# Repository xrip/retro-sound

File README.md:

# RP2040 Retro Sound

## What is?
RP2040 Retro Sound is a project that enables the Raspberry Pi Pico (RP2040) to serve as a COM port passthrough for various FM retro sound chips like the SAA1099, SN76489, YM3812, and YMF262. 

[Interactive BOM (bill of materials)](https://xrip.github.io/retro-sound/hardware/bom/ibom.html)

Assembled PCB:

Gerbers available via releases, or you can use whole KiCad project from ``hardware`` folder

With this setup, you can bring the authentic sound of classic gaming and computing systems to life using original sound chips. Enjoy the nostalgia of retro audio in a modern, convenient package!

## Purpose
The goal of this project is to allow enthusiasts to listen to retro sound with real sound chips without needing any other retro hardware.

## How to use
To use this project, you will need a modified version of <a href="https://github.com/xrip/retro-sound-dosbox-x/tree/master">DosBox-X</a> or a Sega Master System/Sega Genesis emulator that can passthrough sound data directly to the chips via a COM port. COM7 hardcoded right now.

The operation protocol is straightforward and consists of two-byte transfers. The first byte is the command byte:

```
/*
 * 76543210 - command byte
 * ||||||||
 * |||||||+-- chip 0 / chip 1
 * ||||||+--- address or data
 * ||||++---- reserved
 * ++++------ 0x0...0xE chip id:
 *
 *            0x0 - SN76489 (Tandy 3 voice)
 *            0x1 - YM2413 (OPLL)
 *            0x2 - YM3812 (OPL2)
 *            0x3 - SAA1099 (Creative Music System / GameBlaster)
 *            0x4 - YMF262 (OPL3)
 *            0x5 - YM2612, YM2203, YM2608, YM2610, YMF288 (OPN2 and OPN-compatible series)
 *            ...
 *            0xf - all chips reset/initialization
 */
```

The second byte is the data byte, which is routed directly to the chip.

## Requirements
1. PCB (gerbers available via releases, or you can use whole KiCad project from ``hardware`` dir)
2. RP2040 mini: The microcontroller that powers the project.
4. Retro Sound Chips: Choose from SN76489, SAA1099, YM2413, YM3812, YMF262, or any OPN2 compatible chip. The YMF262 is recommended for its versatility. 
5. Capacitors and Resistors: A few passive components for stable operation.
6. Basic Soldering Skills: Minimal soldering is required to assemble the hardware.

## Credits
PCB designs and all hardware stuff are by Sa Gin

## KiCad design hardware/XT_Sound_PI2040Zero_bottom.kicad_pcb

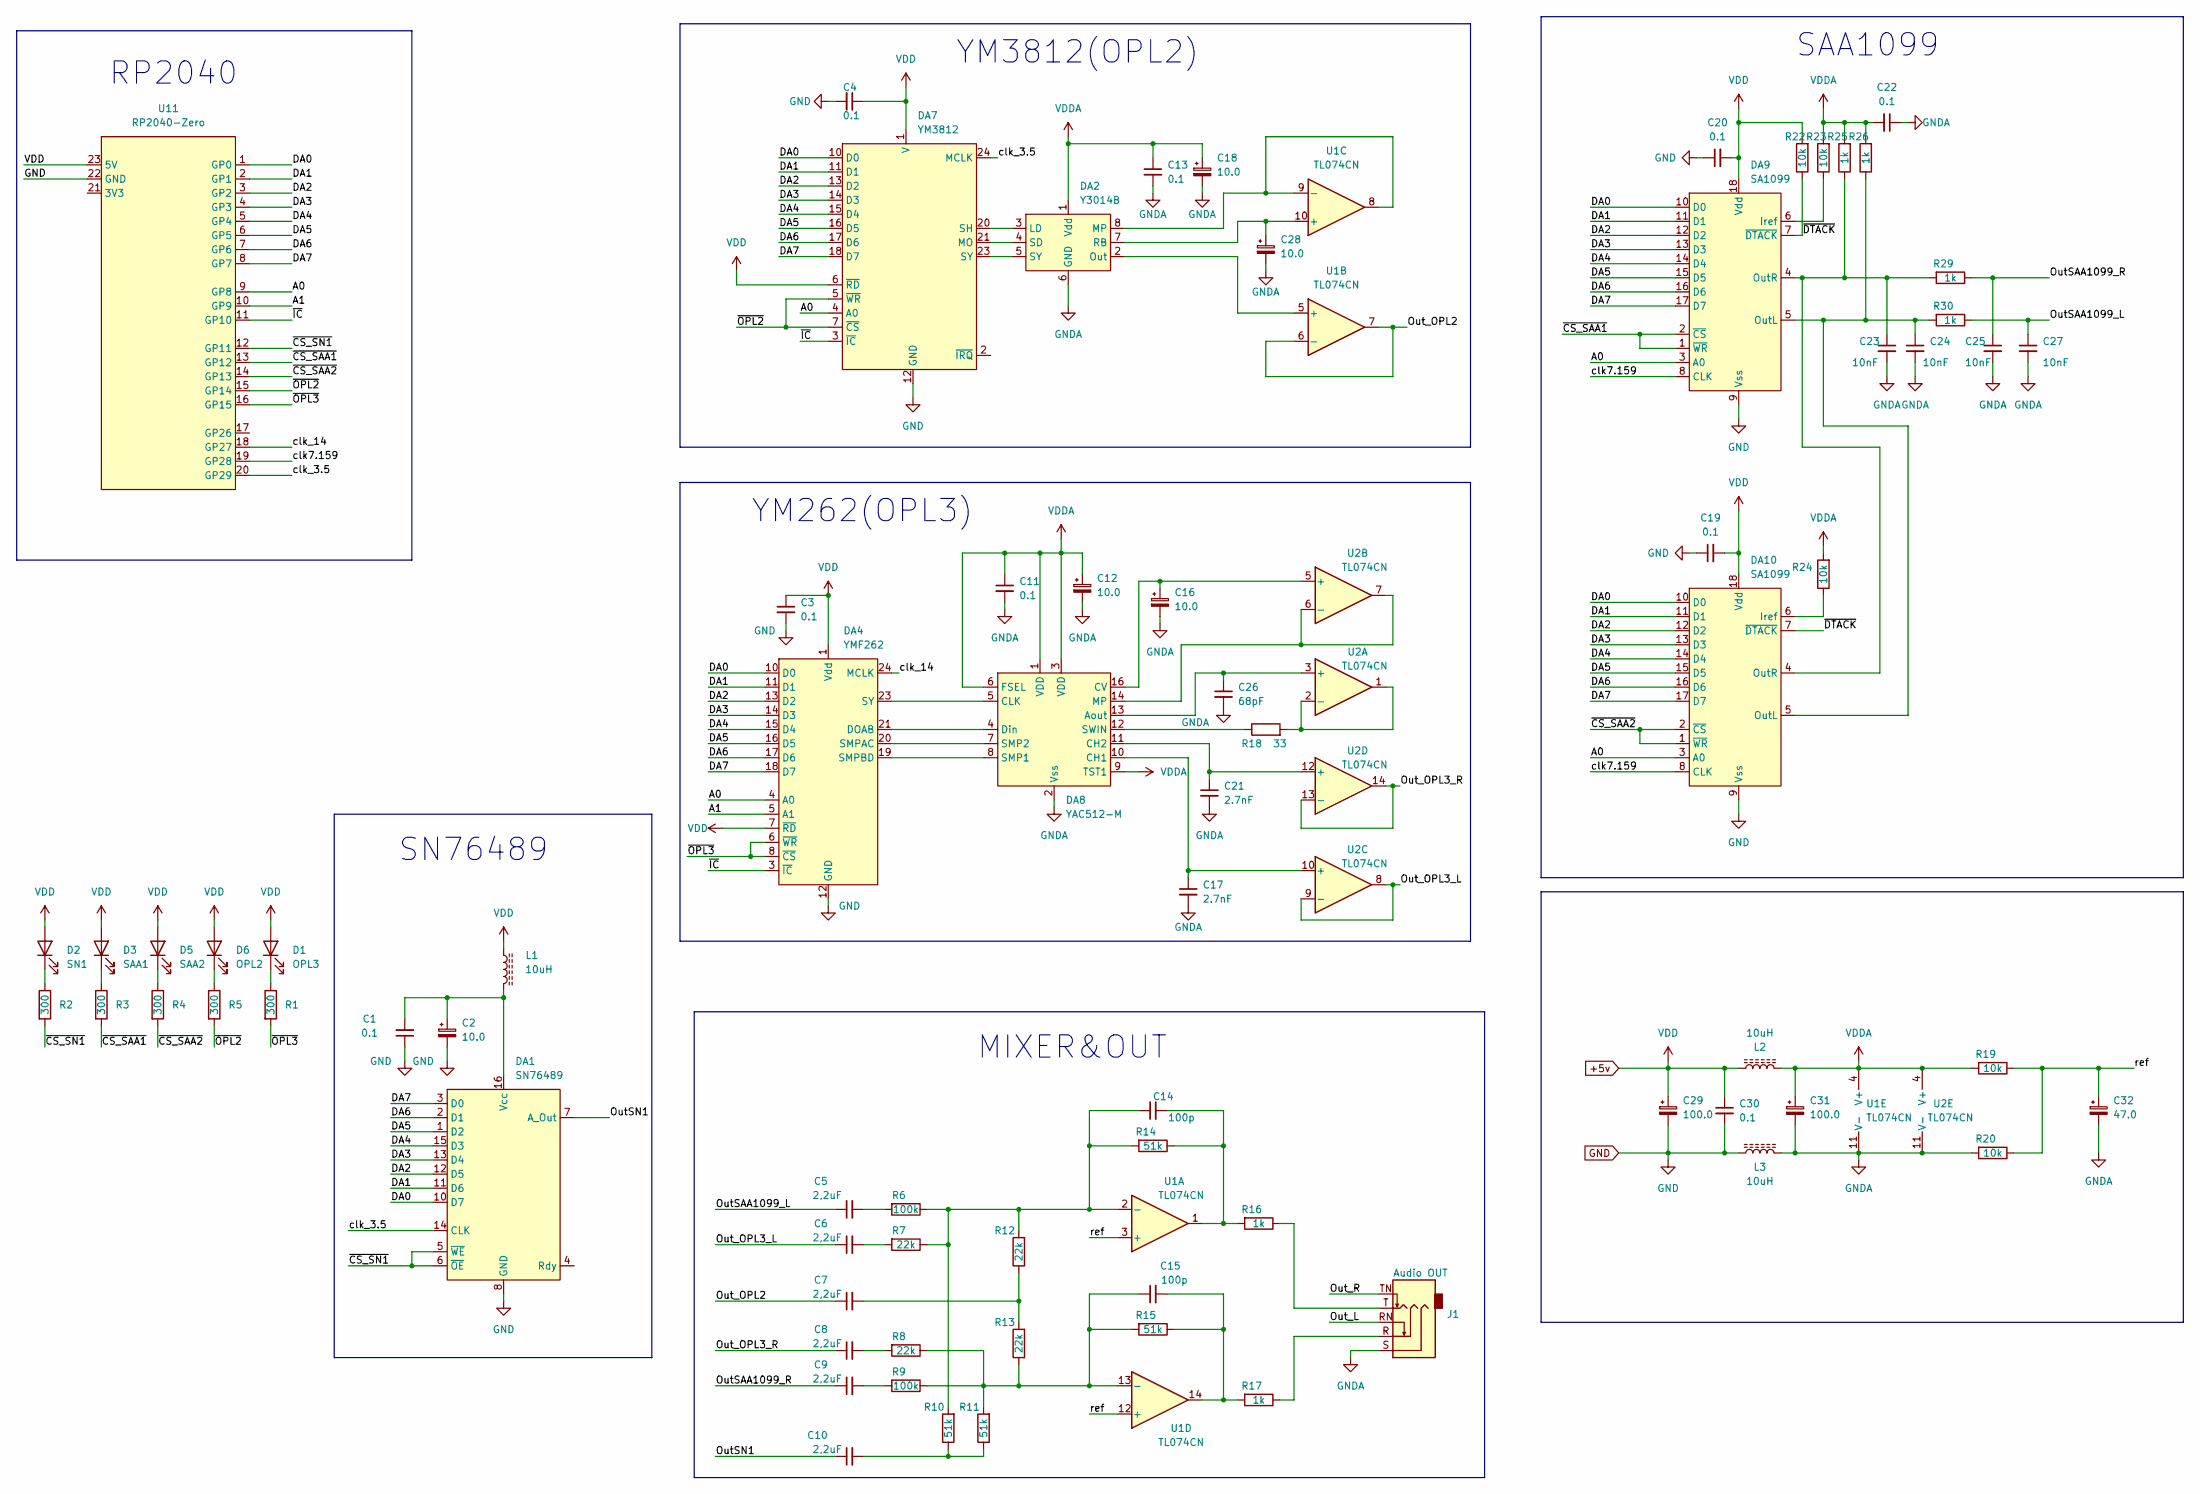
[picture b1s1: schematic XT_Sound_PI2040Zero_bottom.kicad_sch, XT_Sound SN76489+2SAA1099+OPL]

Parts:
C1, C3, C4, C11, C13, C19, C20, C22, C30: 0.1; C_0805_2012Metric_Pad1.18x1.45mm_HandSolder
C2, C12, C16, C18, C28: 10.0; CP_Elec_4x5.4
C5, C6, C7, C8, C9, C10: 2,2uF; C_0805_2012Metric_Pad1.18x1.45mm_HandSolder
C14, C15: 100p; C_0805_2012Metric_Pad1.18x1.45mm_HandSolder
C17, C21: 2.7nF; C_0805_2012Metric_Pad1.18x1.45mm_HandSolder
C23, C24, C25, C27: 10nF; C_0805_2012Metric_Pad1.18x1.45mm_HandSolder
C26: 68pF; C_0805_2012Metric_Pad1.18x1.45mm_HandSolder
C29, C31: 100.0; CP_Elec_5x5.4
C32: 47.0; CP_Elec_5x5.4
D1: OPL3; LED_Rectangular_W5.0mm_H2.0mm
D2: SN1; LED_Rectangular_W5.0mm_H2.0mm
D3: SAA1; LED_Rectangular_W5.0mm_H2.0mm
D5: SAA2; LED_Rectangular_W5.0mm_H2.0mm
D6: OPL2; LED_Rectangular_W5.0mm_H2.0mm
DA1: SN76489; DIP-16_W7.62mm
DA2: Y3014B; DIP-8_W7.62mm_LongPads
DA4: YMF262; SOP-24_7.5x15.4mm_P1.27mm
DA7: YM3812; DIP-24_W15.24mm
DA8: YAC512-M; SOIC-16_4.55x10.3mm_P1.27mm
DA9, DA10: SA1099; DIP-18_W7.62mm
J1: Audio OUT; Jack_3.5mm_CUI_SJ1-3525N_Horizontal
L1, L2, L3: 10uH; L_0805_2012Metric_Pad1.15x1.40mm_HandSolder
R1, R2, R3, R4, R5: 300; R_0805_2012Metric_Pad1.20x1.40mm_HandSolder
R6, R9: 100k; R_0805_2012Metric_Pad1.20x1.40mm_HandSolder
R7, R8, R12, R13: 22k; R_0805_2012Metric_Pad1.20x1.40mm_HandSolder
R10, R11, R14, R15: 51k; R_0805_2012Metric_Pad1.20x1.40mm_HandSolder
R16, R17, R25, R26, R29, R30: 1k; R_0805_2012Metric_Pad1.20x1.40mm_HandSolder
R18: 33; R_0805_2012Metric_Pad1.20x1.40mm_HandSolder
R19, R20, R22, R23, R24: 10k; R_0805_2012Metric_Pad1.20x1.40mm_HandSolder
U1, U2: TL074CN; DIP-14_W7.62mm_Socket
U11: RP2040-Zero

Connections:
+5v: C3.1, C4.1, C19.2, C20.2, C29.1, C30.1, D1.2 (A), D2.2 (A), D3.2 (A), D5.2 (A), D6.2 (A), DA4.1 (Vdd), DA4.7 (~RD), DA7.1 (V), DA7.6 (~RD), DA9.18 (Vdd), DA10.18 (Vdd), L1.1, L2.1, R22.2, U11.23 (5V)
/A0: DA4.4 (A0), DA7.4 (A0), DA9.3 (A0), DA10.3 (A0), U11.9 (GP8)
/A1: DA4.5 (A1), U11.10 (GP9)
/DA0: DA1.10 (D7), DA4.10 (D0), DA7.10 (D0), DA9.10 (D0), DA10.10 (D0), U11.1 (GP0)
/DA1: DA1.11 (D6), DA4.11 (D1), DA7.11 (D1), DA9.11 (D1), DA10.11 (D1), U11.2 (GP1)
/DA2: DA1.12 (D5), DA4.13 (D2), DA7.13 (D2), DA9.12 (D2), DA10.12 (D2), U11.3 (GP2)
/DA3: DA1.13 (D4), DA4.14 (D3), DA7.14 (D3), DA9.13 (D3), DA10.13 (D3), U11.4 (GP3)
/DA4: DA1.15 (D3), DA4.15 (D4), DA7.15 (D4), DA9.14 (D4), DA10.14 (D4), U11.5 (GP4)
/DA5: DA1.1 (D2), DA4.16 (D5), DA7.16 (D5), DA9.15 (D5), DA10.15 (D5), U11.6 (GP5)
/DA6: DA1.2 (D1), DA4.17 (D6), DA7.17 (D6), DA9.16 (D6), DA10.16 (D6), U11.7 (GP6)
/DA7: DA1.3 (D0), DA4.18 (D7), DA7.18 (D7), DA9.17 (D7), DA10.17 (D7), U11.8 (GP7)
/OutSAA1099_L: C5.1, C27.1, R30.1
/OutSAA1099_R: C9.1, C25.1, R29.1
/OutSN1: C10.1, DA1.7 (A_Out)
/Out_L: J1.RN
/Out_OPL2: C7.1, U1.6 (-), U1.7
/Out_OPL3_L: C6.1, U2.8, U2.9 (-)
/Out_OPL3_R: C8.1, U2.13 (-), U2.14
/Out_R: J1.TN
/clk7.159: DA9.8 (CLK), DA10.8 (CLK), U11.19 (GP28)
/clk_3.5: DA1.14 (CLK), DA7.24 (MCLK), U11.20 (GP29)
/clk_14: DA4.24 (MCLK), U11.18 (GP27)
/ref: C32.1, R19.1, R20.1, U1.3 (+), U1.12 (+)
/~CS_SAA1: DA9.1 (~WR), DA9.2 (~CS), R3.2, U11.13 (GP12)
/~CS_SAA2: DA10.1 (~WR), DA10.2 (~CS), R4.2, U11.14 (GP13)
/~CS_SN1: DA1.5 (~WE), DA1.6 (~OE), R2.2, U11.12 (GP11)
/~DTACK: DA9.7 (~DTACK), DA10.7 (~DTACK), R22.1
/~IC: DA4.3 (~IC), DA7.3 (~IC), U11.11 (GP10)
/~OPL2: DA7.5 (~WR), DA7.7 (~CS), R5.2, U11.15 (GP14)
/~OPL3: DA4.6 (~WR), DA4.8 (~CS), R1.2, U11.16 (GP15)
GND: C1.1, C2.2, C3.2, C4.2, C19.1, C20.1, C29.2, C30.2, DA1.8 (GND), DA4.12 (GND), DA7.12 (GND), DA9.9 (Vss), DA10.9 (Vss), L3.1, U11.22 (GND)
GNDA: C11.2, C12.2, C13.2, C16.2, C17.2, C18.2, C21.2, C22.1, C23.2, C24.2, C25.2, C26.2, C27.2, C28.2, C31.2, C32.2, DA2.6 (GND), DA8.2 (Vss), J1.S, L3.2, R20.2, U1.11 (V-), U2.11 (V-)
unnamed: C1.2, C2.1, DA1.16 (Vcc), L1.2
unnamed: C5.2, R6.2
unnamed: C6.2, R7.2
unnamed: C7.2, R12.1, R13.2
unnamed: C8.2, R8.2
unnamed: C9.2, R9.2
unnamed: C10.2, R10.1, R11.1
unnamed: C14.1, R6.1, R7.1, R10.2, R12.2, R14.2, U1.2 (-)
unnamed: C14.2, R14.1, R16.2, U1.1
unnamed: C15.1, R8.1, R9.1, R11.2, R13.1, R15.2, U1.13 (-)
unnamed: C15.2, R15.1, R17.2, U1.14
unnamed: C16.1, DA8.16 (CV), U2.5 (+)
unnamed: C17.1, DA8.10 (CH1), U2.10 (+)
unnamed: C21.1, DA8.11 (CH2), U2.12 (+)
unnamed: C23.1, DA9.4 (OutR), DA10.4 (OutR), R25.1, R29.2
unnamed: C24.1, DA9.5 (OutL), DA10.5 (OutL), R26.1, R30.2
unnamed: C26.1, DA8.13 (Aout), U2.3 (+)
unnamed: C28.1, DA2.7 (RB), U1.10 (+)
unnamed: D1.1 (K), R1.1
unnamed: D2.1 (K), R2.1
unnamed: D3.1 (K), R3.1
unnamed: D5.1 (K), R4.1
unnamed: D6.1 (K), R5.1
unnamed: DA2.2 (Out), U1.5 (+)
unnamed: DA2.3 (LD), DA7.20 (SH)
unnamed: DA2.4 (SD), DA7.21 (MO)
unnamed: DA2.5 (SY), DA7.23 (SY)
unnamed: DA2.8 (MP), U1.8, U1.9 (-)
unnamed: DA4.19 (SMPBD), DA8.8 (SMP1)
unnamed: DA4.20 (SMPAC), DA8.7 (SMP2)
unnamed: DA4.21 (DOAB), DA8.4 (Din)
unnamed: DA4.23 (SY), DA8.5 (CLK)
unnamed: DA8.12 (SWIN), R18.1
unnamed: DA8.14 (MP), U2.6 (-), U2.7
unnamed: DA9.6 (Iref), R23.1
unnamed: DA10.6 (Iref), R24.1
unnamed: J1.R, R17.1
unnamed: J1.T, R16.1
unnamed: R18.2, U2.1, U2.2 (-)
VDDA: C11.1, C12.1, C13.1, C18.1, C22.2, C31.1, DA2.1 (Vdd), DA8.1 (VDD), DA8.3 (VDD), DA8.6 (FSEL), DA8.9 (TST1), L2.2, R19.2, R23.2, R24.2, R25.2, R26.2, U1.4 (V+), U2.4 (V+)

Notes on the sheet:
YM262(OPL3)
YM3812(OPL2)
MIXER&OUT
SAA1099
RP2040
SN76489

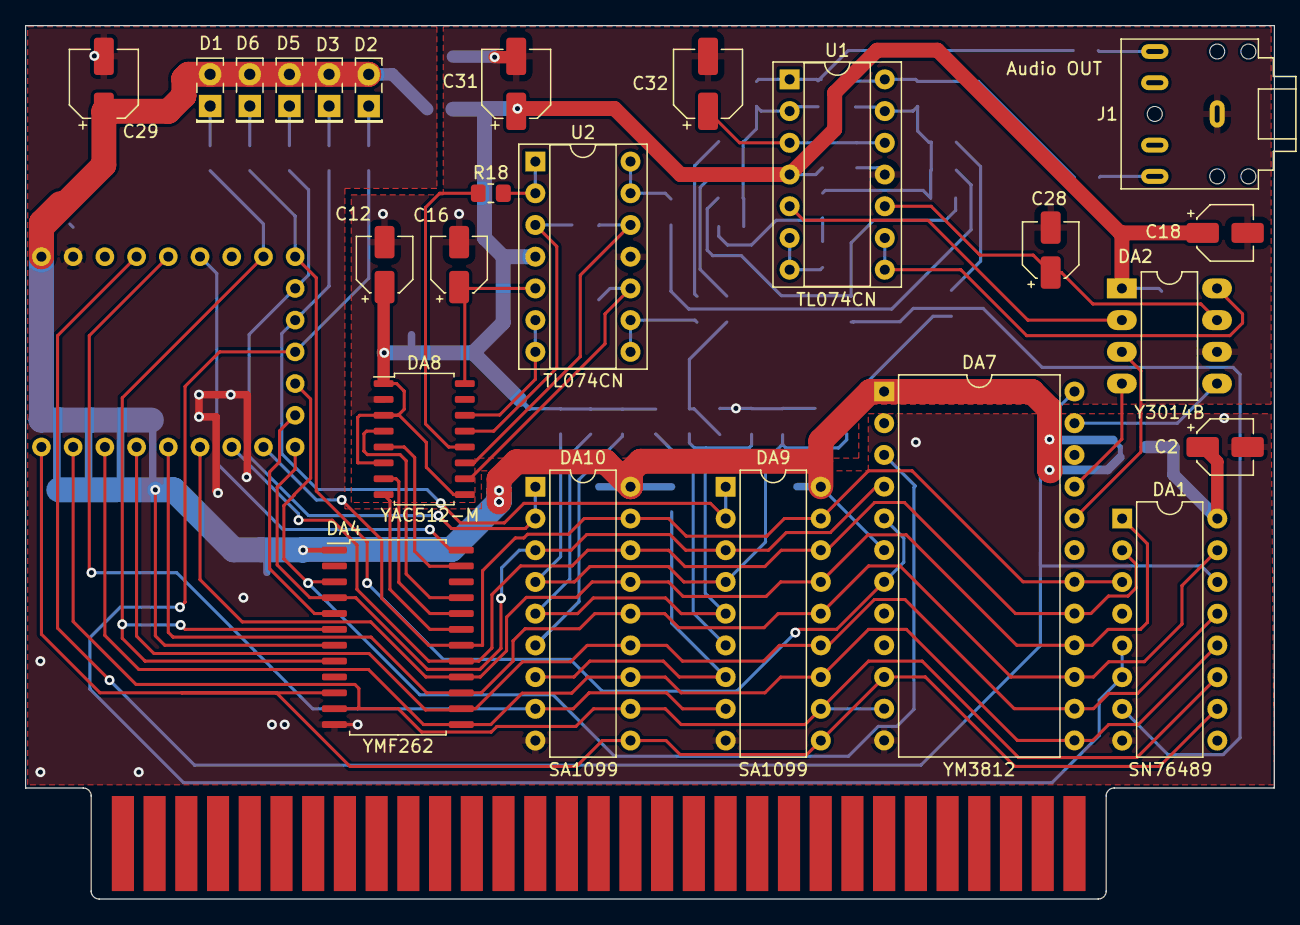
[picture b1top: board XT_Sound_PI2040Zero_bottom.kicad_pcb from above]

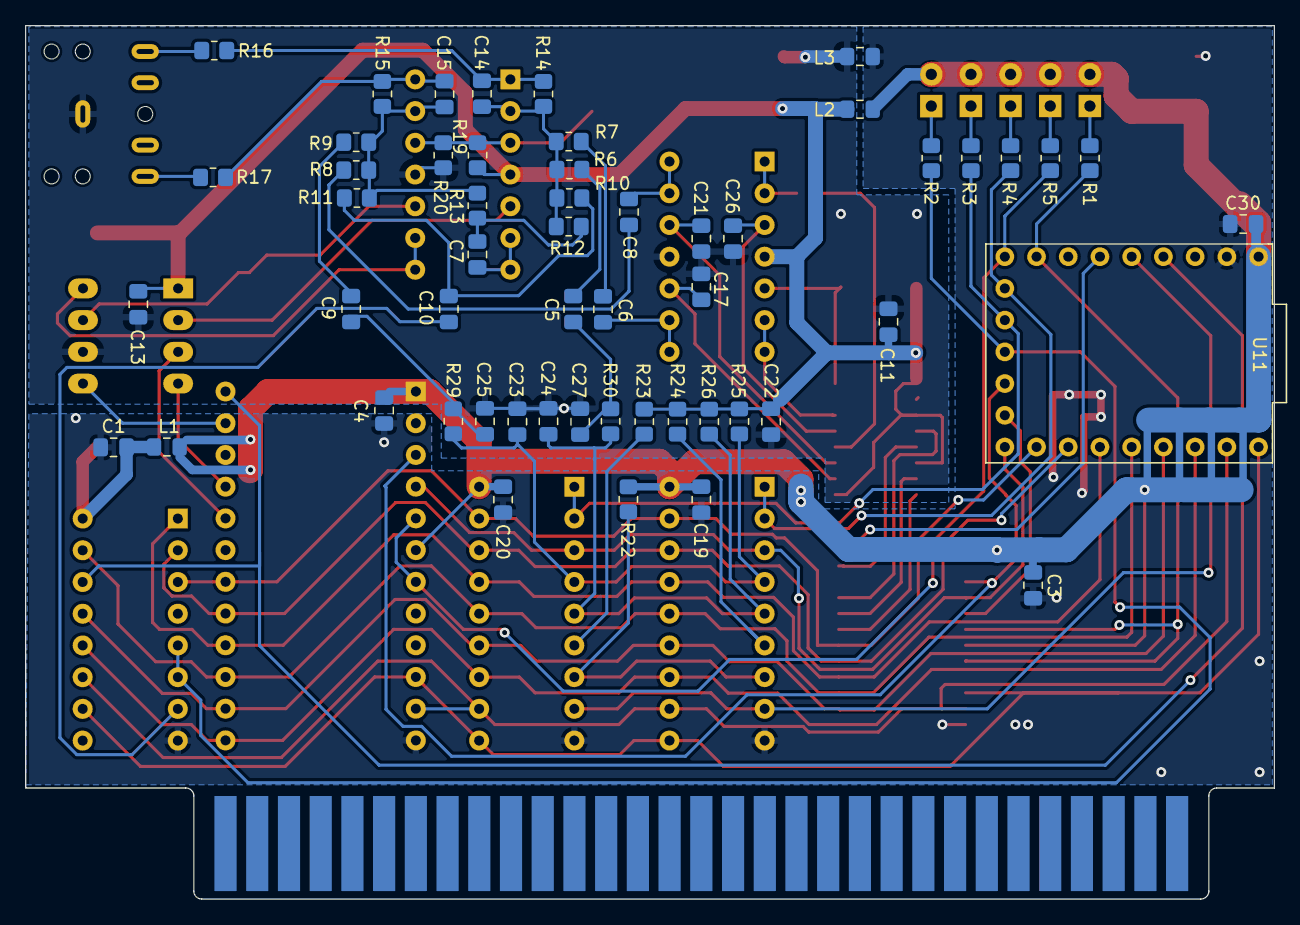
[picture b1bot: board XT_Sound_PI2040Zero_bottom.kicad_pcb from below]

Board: 2 copper layers, 100.0 x 69.9 mm, 78 parts (54 on the bottom side), 70 nets.

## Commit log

2024-06-10 Sonic 1 Greeh Hills
2024-06-10 improvements
2024-06-12 pio version
2024-06-13 simplified
2024-06-13 adlib
2024-06-17 working
2024-06-17 passthru working
2024-06-18 cleanup
2024-06-18 pinout added
2024-06-20 fake ay
2024-06-21 ym preparations
2024-06-21 clenup
2024-06-24 2xSAA
2024-06-25 ym2413
2024-06-26 sega master system support
2024-06-27 global control bits
2024-06-27 Readme1
2024-06-27 Readme
2024-06-27 tandy
2024-06-28 ym2413 saa1099
2024-06-28 ym2612
2024-07-01 ym3812
2024-07-11 delay with pio
2024-07-15 refactoring and optimizations
2024-07-17 Optimizations
2024-07-22 compile-time optimizations
2024-07-23 dynamic clock setup
2025-01-14 kicad shcematics added
2025-01-16 RP2040 zero
2025-01-16 lookup for pico_sdk_import.cmake within env
2025-01-16 ws2812 colors adjusted
2025-01-16 Create CNAME
